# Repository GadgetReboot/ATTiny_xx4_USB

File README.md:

# ATTiny_xx4_USB
ATTiny 14 pin device USB breakout pcb for 0-Series and 1-Series

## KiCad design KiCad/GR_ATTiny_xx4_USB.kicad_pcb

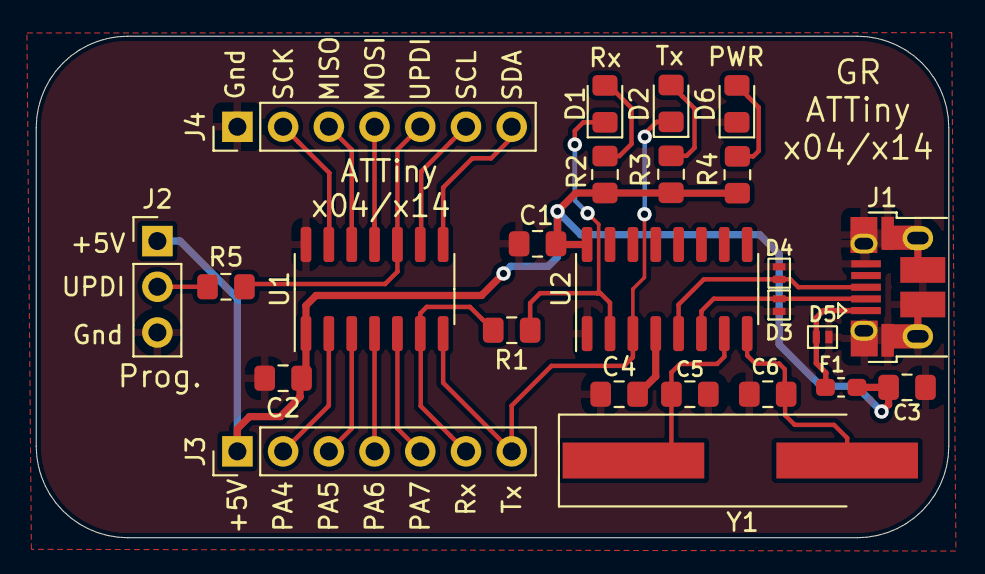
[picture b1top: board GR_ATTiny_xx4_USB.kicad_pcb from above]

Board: 2 copper layers, 50.7 x 27.9 mm, 25 parts (0 on the bottom side), 25 nets.

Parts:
C1, C2, C4: 100nF; C_0805_2012Metric_Pad1.15x1.40mm_HandSolder
C3: 1uF; C_0805_2012Metric_Pad1.15x1.40mm_HandSolder
C5, C6: 22pF; C_0805_2012Metric_Pad1.15x1.40mm_HandSolder
D1: Rx; LED_0805_2012Metric_Pad1.15x1.40mm_HandSolder
D2: Tx; LED_0805_2012Metric_Pad1.15x1.40mm_HandSolder
D3, D4, D5: PESD5V0S1BL; SOD-882
D6: Power; LED_0805_2012Metric_Pad1.15x1.40mm_HandSolder
F1: MF-FSMF050X; R_0603_1608Metric_Pad1.05x0.95mm_HandSolder
J1: USB_B_Micro; USB_Micro-B_Amphenol_10103594-0001LF_Horizontal
J2: Conn_01x03; PinHeader_1x03_P2.54mm_Vertical
J3, J4: Conn_01x07; PinHeader_1x07_P2.54mm_Vertical
R1, R2, R3, R4, R5: 1K; R_0805_2012Metric_Pad1.15x1.40mm_HandSolder
U1: ATtiny x04/x14; SOIC-14_3.9x8.7mm_P1.27mm
U2: CH340G; SOIC-16_3.9x9.9mm_P1.27mm
Y1: 12MHz; Crystal_SMD_HC49-SD_HandSoldering

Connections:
+5V: C1.1, C2.1, C3.1, F1.2, J2.1, J3.1, R2.2, R3.2, R4.1, U1.1, U2.16
/MISO: J4.3, U1.12
/MOSI: J4.4, U1.11
/PA4: J3.2, U1.2
/PA5: J3.3, U1.3
/PA6: J3.4, U1.4
/PA7: J3.5, U1.5
/RX_In: J3.6, R1.2, U1.6
/SCK: J4.2, U1.13
/SCL: J4.6, U1.9
/SDA: J4.7, U1.8
/TX_Out: D2.1, J3.7, U1.7, U2.3
/UPDI: J4.5, R5.2, U1.10
GNDREF: C1.2, C2.2, C3.2, C4.2, C5.2, C6.2, D3.2, D4.2, D5.2, D6.1, J1.5, J1.6, J2.3, J4.1, U1.14, U2.1
unnamed: C4.1, U2.4
unnamed: C5.1, U2.7, Y1.1
unnamed: C6.1, U2.8, Y1.2
unnamed: D1.1, R1.1, U2.2
unnamed: D1.2, R2.1
unnamed: D2.2, R3.1
unnamed: D3.1, J1.2, U2.6
unnamed: D4.1, J1.3, U2.5
unnamed: D5.1, F1.1, J1.1
unnamed: D6.2, R4.2
unnamed: J2.2, R5.1
